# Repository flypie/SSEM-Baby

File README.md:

# SSEM-Baby

This is a work in progress.

All of the IP belongs to the Computer Conservation Society this project is purely to convert the diagrams to KiCAD as a format with greater utility. https://computerconservationsociety.org/ssemvolunteers/volunteers/index.html

I do not claim any rights whatsoever.

If anyone want to do help out with checks or corrections let me know and I'll try and work out how Merge works.

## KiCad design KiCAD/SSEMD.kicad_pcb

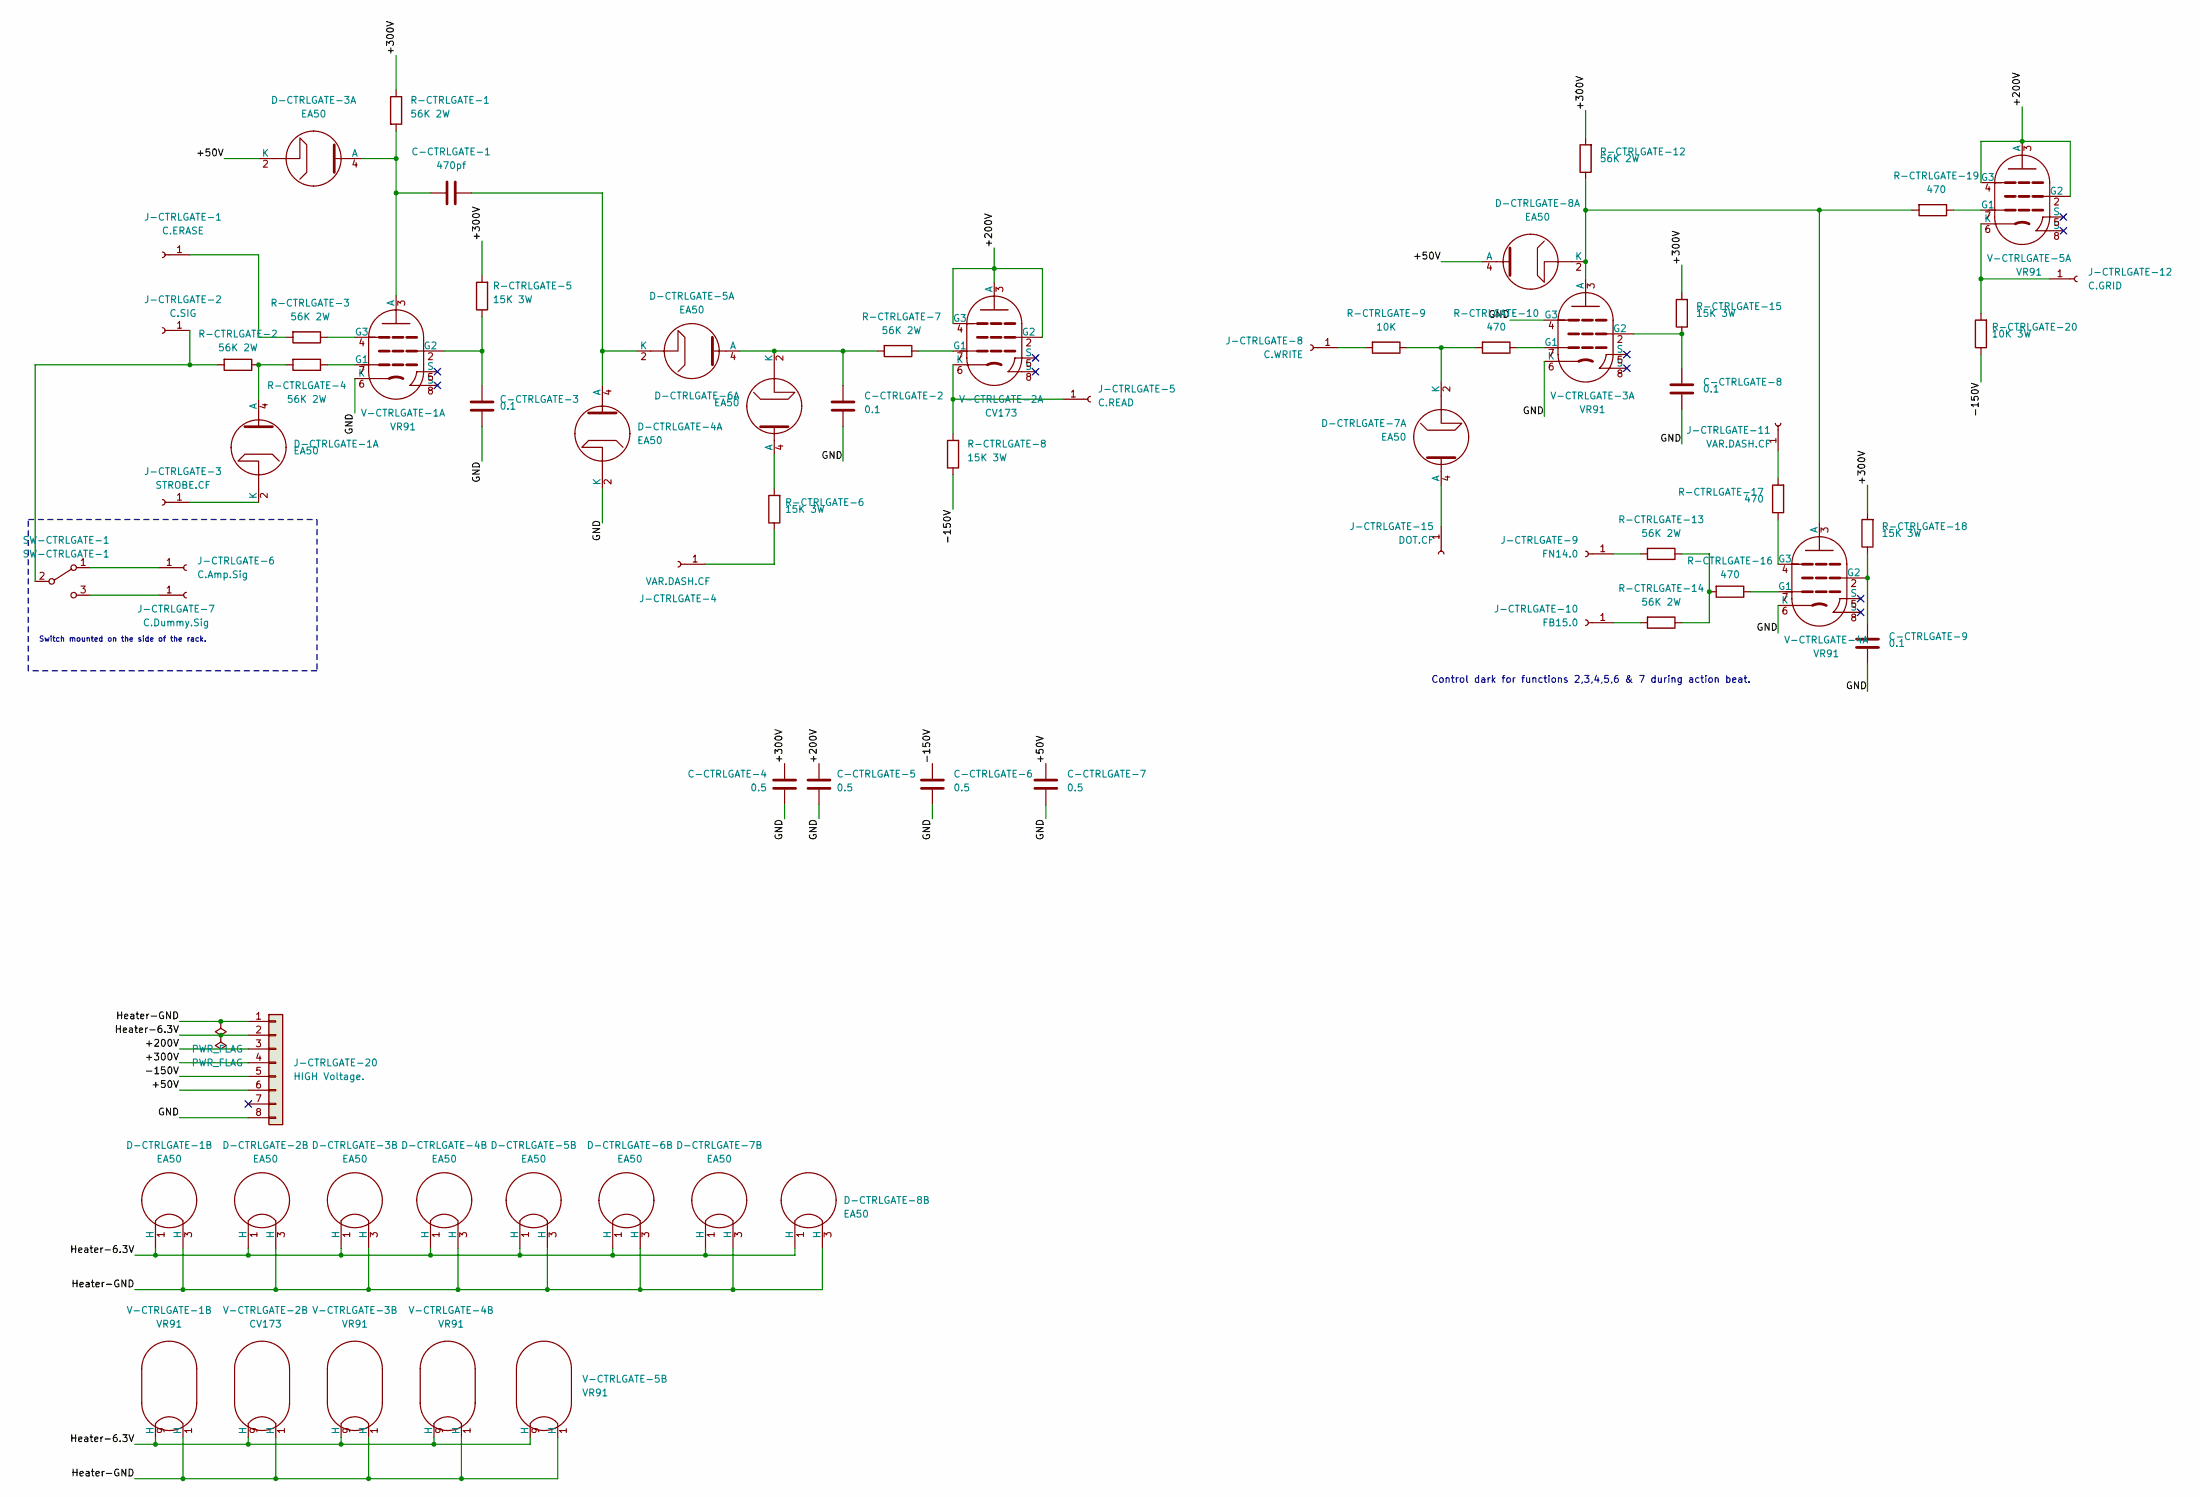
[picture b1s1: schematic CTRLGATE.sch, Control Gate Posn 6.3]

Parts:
C-CTRLGATE-1: 470pf; C_Disc_D7.5mm_W5.0mm_P5.00mm
C-CTRLGATE-2, C-CTRLGATE-3, C-CTRLGATE-8, C-CTRLGATE-9: 0.1; C_Disc_D7.5mm_W5.0mm_P5.00mm
C-CTRLGATE-4, C-CTRLGATE-5, C-CTRLGATE-6, C-CTRLGATE-7: 0.5; C_Disc_D7.5mm_W5.0mm_P5.00mm
D-CTRLGATE-1, D-CTRLGATE-2, D-CTRLGATE-3, D-CTRLGATE-4, D-CTRLGATE-5, D-CTRLGATE-6, D-CTRLGATE-7, D-CTRLGATE-8: EA50; Valve_B3G
J-CTRLGATE-1: C.ERASE; 242431
J-CTRLGATE-2: C.SIG; 242431
J-CTRLGATE-3: STROBE.CF; 242431
J-CTRLGATE-4, J-CTRLGATE-11: VAR.DASH.CF; 242431
J-CTRLGATE-5: C.READ; 242431
J-CTRLGATE-6: C.Amp.Sig; 242431
J-CTRLGATE-7: C.Dummy.Sig; 242431
J-CTRLGATE-8: C.WRITE; 242431
J-CTRLGATE-9: FN14.0; 242431
J-CTRLGATE-10: FB15.0; 242431
J-CTRLGATE-12: C.GRID; 242431
J-CTRLGATE-15: DOT.CF; 242431
J-CTRLGATE-20: HIGH Voltage.; TE_MATE-N-LOK_1-770970-x_2x04_P4.14mm_Horizontal
R-CTRLGATE-1, R-CTRLGATE-2, R-CTRLGATE-3, R-CTRLGATE-4, R-CTRLGATE-7, R-CTRLGATE-12, R-CTRLGATE-13, R-CTRLGATE-14: 56K 2W; R_Axial_DIN0516_L15.5mm_D5.0mm_P5.08mm_Vertical
R-CTRLGATE-5, R-CTRLGATE-6, R-CTRLGATE-8, R-CTRLGATE-15, R-CTRLGATE-18: 15K 3W; R_Axial_DIN0516_L15.5mm_D5.0mm_P5.08mm_Vertical
R-CTRLGATE-9: 10K; R_Axial_DIN0516_L15.5mm_D5.0mm_P5.08mm_Vertical
R-CTRLGATE-10, R-CTRLGATE-16, R-CTRLGATE-17, R-CTRLGATE-19: 470; R_Axial_DIN0516_L15.5mm_D5.0mm_P5.08mm_Vertical
R-CTRLGATE-20: 10K 3W; R_Axial_DIN0516_L15.5mm_D5.0mm_P5.08mm_Vertical
SW-CTRLGATE-1: SW-CTRLGATE-1; M2011SS1W03
V-CTRLGATE-1, V-CTRLGATE-3, V-CTRLGATE-4, V-CTRLGATE-5: VR91; Valve_9Loctal
V-CTRLGATE-2: CV173; Valve_9Loctal

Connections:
/CTRLGATE/+50V: C-CTRLGATE-7.1, D-CTRLGATE-3.2 (K), D-CTRLGATE-8.4 (A), J-CTRLGATE-20.6
/CTRLGATE/+200V: C-CTRLGATE-5.1, J-CTRLGATE-20.3, V-CTRLGATE-2.2 (G2), V-CTRLGATE-2.3 (A), V-CTRLGATE-2.4 (G3), V-CTRLGATE-5.2 (G2), V-CTRLGATE-5.3 (A), V-CTRLGATE-5.4 (G3)
/CTRLGATE/+300V: C-CTRLGATE-4.1, J-CTRLGATE-20.4, R-CTRLGATE-1.1, R-CTRLGATE-5.2, R-CTRLGATE-12.2, R-CTRLGATE-15.2, R-CTRLGATE-18.2
/CTRLGATE/-150V: C-CTRLGATE-6.2, J-CTRLGATE-20.5, R-CTRLGATE-8.1, R-CTRLGATE-20.1
/CTRLGATE/GND: C-CTRLGATE-2.2, C-CTRLGATE-3.2, C-CTRLGATE-4.2, C-CTRLGATE-5.2, C-CTRLGATE-6.1, C-CTRLGATE-7.2, C-CTRLGATE-8.2, C-CTRLGATE-9.2, D-CTRLGATE-4.2 (K), J-CTRLGATE-20.8, V-CTRLGATE-1.6 (K), V-CTRLGATE-3.4 (G3), V-CTRLGATE-3.6 (K), V-CTRLGATE-4.6 (K)
/CTRLGATE/Heater-6.3V: D-CTRLGATE-1.1 (H), D-CTRLGATE-2.1 (H), D-CTRLGATE-3.1 (H), D-CTRLGATE-4.1 (H), D-CTRLGATE-5.1 (H), D-CTRLGATE-6.1 (H), D-CTRLGATE-7.1 (H), D-CTRLGATE-8.1 (H), J-CTRLGATE-20.2, V-CTRLGATE-1.9 (H), V-CTRLGATE-2.9 (H), V-CTRLGATE-3.9 (H), V-CTRLGATE-4.9 (H), V-CTRLGATE-5.9 (H)
/CTRLGATE/Heater-GND: D-CTRLGATE-1.3 (H), D-CTRLGATE-2.3 (H), D-CTRLGATE-3.3 (H), D-CTRLGATE-4.3 (H), D-CTRLGATE-5.3 (H), D-CTRLGATE-6.3 (H), D-CTRLGATE-7.3 (H), D-CTRLGATE-8.3 (H), J-CTRLGATE-20.1, V-CTRLGATE-1.1 (H), V-CTRLGATE-2.1 (H), V-CTRLGATE-3.1 (H), V-CTRLGATE-4.1 (H), V-CTRLGATE-5.1 (H)
unnamed: C-CTRLGATE-1.1, D-CTRLGATE-3.4 (A), R-CTRLGATE-1.2, V-CTRLGATE-1.3 (A)
unnamed: C-CTRLGATE-1.2, D-CTRLGATE-4.4 (A), D-CTRLGATE-5.2 (K)
unnamed: C-CTRLGATE-2.1, D-CTRLGATE-5.4 (A), D-CTRLGATE-6.2 (K), R-CTRLGATE-7.2
unnamed: C-CTRLGATE-3.1, R-CTRLGATE-5.1, V-CTRLGATE-1.2 (G2)
unnamed: C-CTRLGATE-8.1, R-CTRLGATE-15.1, V-CTRLGATE-3.2 (G2)
unnamed: C-CTRLGATE-9.1, R-CTRLGATE-18.1, V-CTRLGATE-4.2 (G2)
unnamed: D-CTRLGATE-1.2 (K), J-CTRLGATE-3.1
unnamed: D-CTRLGATE-1.4 (A), R-CTRLGATE-2.1, R-CTRLGATE-4.2
unnamed: D-CTRLGATE-6.4 (A), R-CTRLGATE-6.2
unnamed: D-CTRLGATE-7.2 (K), R-CTRLGATE-9.1, R-CTRLGATE-10.2
unnamed: D-CTRLGATE-7.4 (A), J-CTRLGATE-15.1
unnamed: D-CTRLGATE-8.2 (K), R-CTRLGATE-12.1, R-CTRLGATE-19.2, V-CTRLGATE-3.3 (A), V-CTRLGATE-4.3 (A)
unnamed: J-CTRLGATE-1.1, R-CTRLGATE-3.2
unnamed: J-CTRLGATE-2.1, R-CTRLGATE-2.2, SW-CTRLGATE-1.2 (B)
unnamed: J-CTRLGATE-4.1, R-CTRLGATE-6.1
unnamed: J-CTRLGATE-5.1, R-CTRLGATE-8.2, V-CTRLGATE-2.6 (K)
unnamed: J-CTRLGATE-6.1, SW-CTRLGATE-1.1 (A)
unnamed: J-CTRLGATE-7.1, SW-CTRLGATE-1.3 (C)
unnamed: J-CTRLGATE-8.1, R-CTRLGATE-9.2
unnamed: J-CTRLGATE-9.1, R-CTRLGATE-13.2
unnamed: J-CTRLGATE-10.1, R-CTRLGATE-14.2
unnamed: J-CTRLGATE-11.1, R-CTRLGATE-17.2
unnamed: J-CTRLGATE-12.1, R-CTRLGATE-20.2, V-CTRLGATE-5.6 (K)
unnamed: R-CTRLGATE-3.1, V-CTRLGATE-1.4 (G3)
unnamed: R-CTRLGATE-4.1, V-CTRLGATE-1.7 (G1)
unnamed: R-CTRLGATE-7.1, V-CTRLGATE-2.7 (G1)
unnamed: R-CTRLGATE-10.1, V-CTRLGATE-3.7 (G1)
unnamed: R-CTRLGATE-13.1, R-CTRLGATE-14.1, R-CTRLGATE-16.2
unnamed: R-CTRLGATE-16.1, V-CTRLGATE-4.7 (G1)
unnamed: R-CTRLGATE-17.1, V-CTRLGATE-4.4 (G3)
unnamed: R-CTRLGATE-19.1, V-CTRLGATE-5.7 (G1)

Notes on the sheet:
Switch mounted on the side of the rack.
Control dark for functions 2,3,4,5,6 & 7 during action beat.

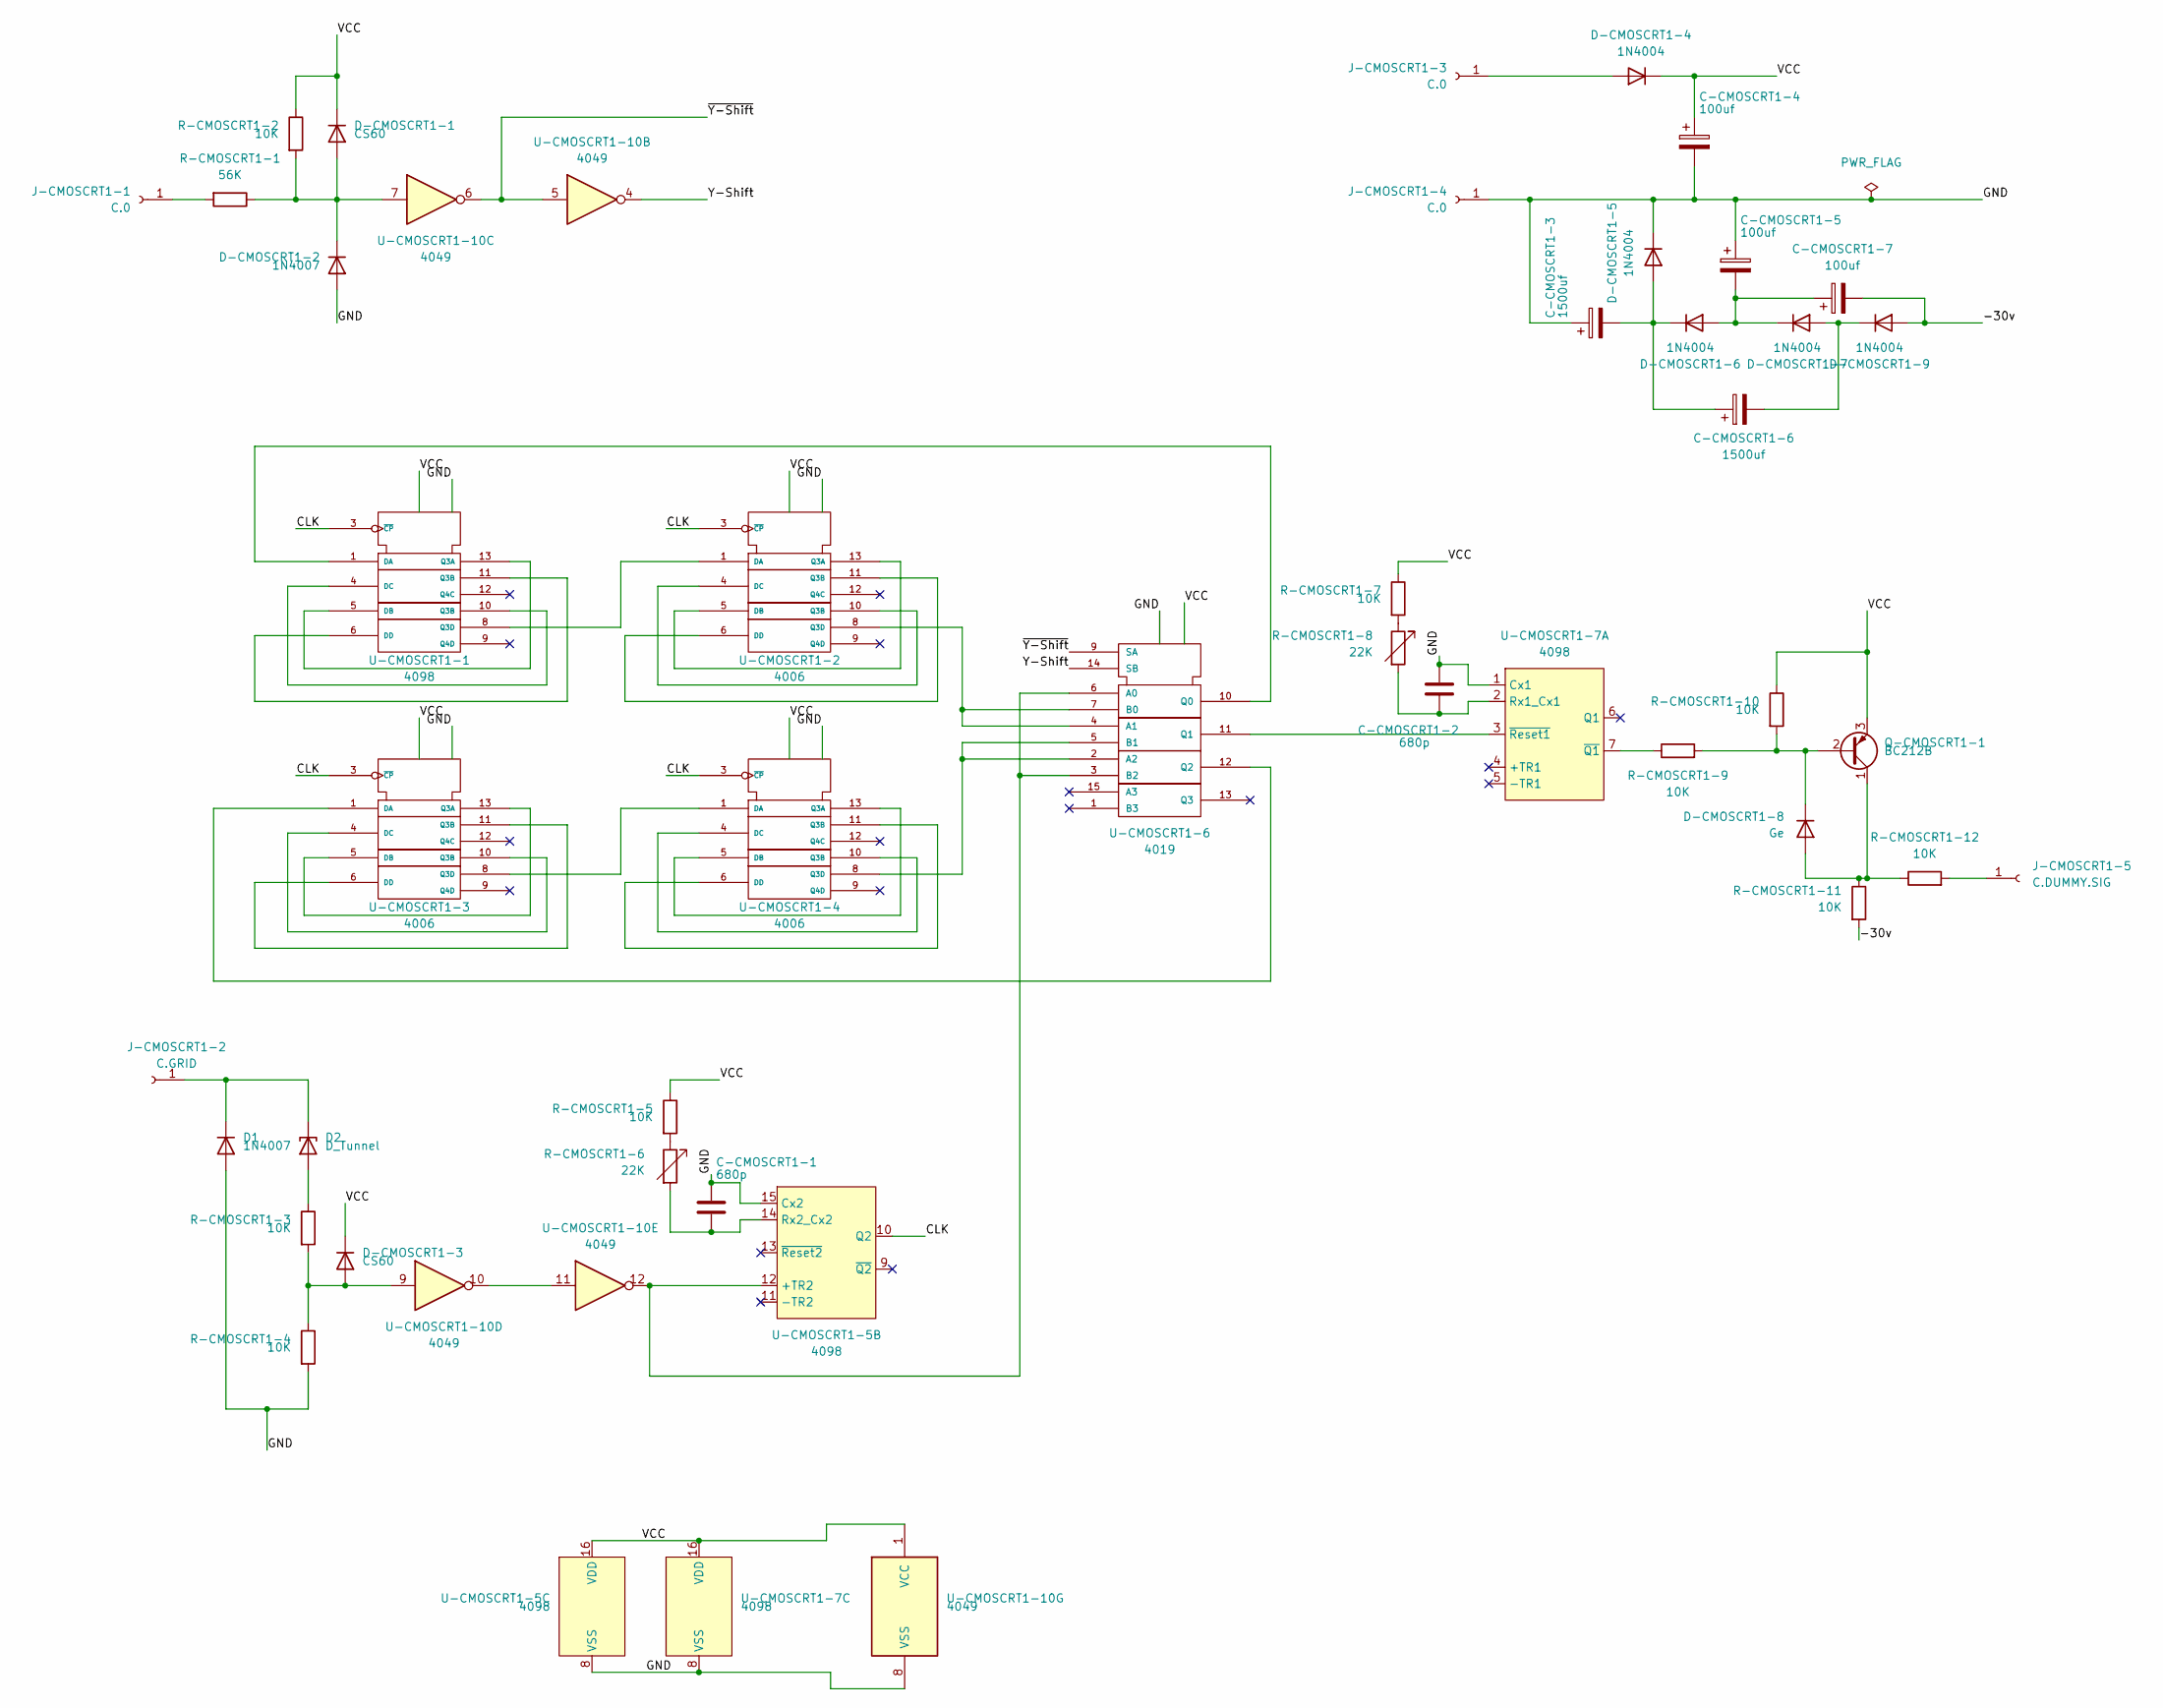
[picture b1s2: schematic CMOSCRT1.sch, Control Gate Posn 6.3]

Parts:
C-CMOSCRT1-1, C-CMOSCRT1-2: 680p; C_Disc_D7.5mm_W5.0mm_P5.00mm
C-CMOSCRT1-3, C-CMOSCRT1-6: 1500uf; C_Disc_D7.5mm_W5.0mm_P5.00mm
C-CMOSCRT1-4, C-CMOSCRT1-5, C-CMOSCRT1-7: 100uf; C_Disc_D7.5mm_W5.0mm_P5.00mm
D1: 1N4007; D_DO-41_SOD81_P10.16mm_Horizontal
D2: D_Tunnel; D_DO-201_P15.24mm_Horizontal
D-CMOSCRT1-1, D-CMOSCRT1-3: CS60; D_T-1_P5.08mm_Horizontal
D-CMOSCRT1-2: 1N4007; D_DO-41_SOD81_P10.16mm_Horizontal
D-CMOSCRT1-4, D-CMOSCRT1-5, D-CMOSCRT1-6, D-CMOSCRT1-7, D-CMOSCRT1-9: 1N4004; D_DO-41_SOD81_P10.16mm_Horizontal
D-CMOSCRT1-8: Ge; D_DO-41_SOD81_P10.16mm_Horizontal
J-CMOSCRT1-1, J-CMOSCRT1-3, J-CMOSCRT1-4: C.0; 242431
J-CMOSCRT1-2: C.GRID; 242431
J-CMOSCRT1-5: C.DUMMY.SIG; 242431
Q-CMOSCRT1-1: BC212B; TO-92_Inline
R-CMOSCRT1-1: 56K; R_Axial_DIN0516_L15.5mm_D5.0mm_P5.08mm_Vertical
R-CMOSCRT1-2, R-CMOSCRT1-3, R-CMOSCRT1-4, R-CMOSCRT1-5, R-CMOSCRT1-7, R-CMOSCRT1-9, R-CMOSCRT1-10, R-CMOSCRT1-11, R-CMOSCRT1-12: 10K; R_Axial_DIN0516_L15.5mm_D5.0mm_P5.08mm_Vertical
R-CMOSCRT1-6, R-CMOSCRT1-8: 22K; R_Axial_DIN0516_L15.5mm_D5.0mm_P5.08mm_Vertical
U-CMOSCRT1-1: 4098; DIP-14_W7.62mm
U-CMOSCRT1-2, U-CMOSCRT1-3, U-CMOSCRT1-4: 4006; DIP-14_W7.62mm
U-CMOSCRT1-5, U-CMOSCRT1-7: 4098; DIP-16_W7.62mm
U-CMOSCRT1-6: 4019; DIP-16_W7.62mm
U-CMOSCRT1-10: 4049; DIP-14_W7.62mm

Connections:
/CMOSCRT1/-30v: C-CMOSCRT1-7.2, D-CMOSCRT1-9.2 (A), R-CMOSCRT1-11.2
/CMOSCRT1/CLK: U-CMOSCRT1-1.3 (~CP), U-CMOSCRT1-2.3 (~CP), U-CMOSCRT1-3.3 (~CP), U-CMOSCRT1-4.3 (~CP), U-CMOSCRT1-5.10 (Q2)
/CMOSCRT1/Y-Shift: U-CMOSCRT1-6.14 (SB), U-CMOSCRT1-10.4
/CMOSCRT1/~Y-Shift: U-CMOSCRT1-6.9 (SA), U-CMOSCRT1-10.5, U-CMOSCRT1-10.6
unnamed: C-CMOSCRT1-1.2, R-CMOSCRT1-6.2, U-CMOSCRT1-5.14 (Rx2_Cx2)
unnamed: C-CMOSCRT1-2.2, R-CMOSCRT1-8.2, U-CMOSCRT1-7.2 (Rx1_Cx1)
unnamed: C-CMOSCRT1-3.2, C-CMOSCRT1-6.1, D-CMOSCRT1-5.2 (A), D-CMOSCRT1-6.1 (K)
unnamed: C-CMOSCRT1-5.2, C-CMOSCRT1-7.1, D-CMOSCRT1-6.2 (A), D-CMOSCRT1-7.1 (K)
unnamed: C-CMOSCRT1-6.2, D-CMOSCRT1-7.2 (A), D-CMOSCRT1-9.1 (K)
unnamed: D1.1 (K), D2.1 (K), J-CMOSCRT1-2.1
unnamed: D2.2 (A), R-CMOSCRT1-3.1
unnamed: D-CMOSCRT1-1.2 (A), D-CMOSCRT1-2.1 (K), R-CMOSCRT1-1.1, R-CMOSCRT1-2.2, U-CMOSCRT1-10.7
unnamed: D-CMOSCRT1-3.2 (A), R-CMOSCRT1-3.2, R-CMOSCRT1-4.1, U-CMOSCRT1-10.9
unnamed: D-CMOSCRT1-4.2 (A), J-CMOSCRT1-3.1
unnamed: D-CMOSCRT1-8.1 (K), Q-CMOSCRT1-1.2 (B), R-CMOSCRT1-9.2, R-CMOSCRT1-10.2
unnamed: D-CMOSCRT1-8.2 (A), Q-CMOSCRT1-1.1 (C), R-CMOSCRT1-11.1, R-CMOSCRT1-12.1
unnamed: J-CMOSCRT1-1.1, R-CMOSCRT1-1.2
unnamed: J-CMOSCRT1-5.1, R-CMOSCRT1-12.2
unnamed: R-CMOSCRT1-5.2, R-CMOSCRT1-6.1
unnamed: R-CMOSCRT1-7.2, R-CMOSCRT1-8.1
unnamed: R-CMOSCRT1-9.1, U-CMOSCRT1-7.7 (~Q1)
unnamed: U-CMOSCRT1-1.1 (DA), U-CMOSCRT1-6.10 (Q0)
unnamed: U-CMOSCRT1-1.8 (Q3D), U-CMOSCRT1-2.1 (DA)
unnamed: U-CMOSCRT1-1.4 (DC), U-CMOSCRT1-1.10 (Q3B)
unnamed: U-CMOSCRT1-1.6 (DD), U-CMOSCRT1-1.11 (Q3B)
unnamed: U-CMOSCRT1-1.5 (DB), U-CMOSCRT1-1.13 (Q3A)
unnamed: U-CMOSCRT1-2.8 (Q3D), U-CMOSCRT1-6.4 (A1), U-CMOSCRT1-6.7 (B0)
unnamed: U-CMOSCRT1-2.4 (DC), U-CMOSCRT1-2.10 (Q3B)
unnamed: U-CMOSCRT1-2.6 (DD), U-CMOSCRT1-2.11 (Q3B)
unnamed: U-CMOSCRT1-2.5 (DB), U-CMOSCRT1-2.13 (Q3A)
unnamed: U-CMOSCRT1-3.1 (DA), U-CMOSCRT1-6.12 (Q2)
unnamed: U-CMOSCRT1-3.8 (Q3D), U-CMOSCRT1-4.1 (DA)
unnamed: U-CMOSCRT1-3.4 (DC), U-CMOSCRT1-3.10 (Q3B)
unnamed: U-CMOSCRT1-3.6 (DD), U-CMOSCRT1-3.11 (Q3B)
unnamed: U-CMOSCRT1-3.5 (DB), U-CMOSCRT1-3.13 (Q3A)
unnamed: U-CMOSCRT1-4.8 (Q3D), U-CMOSCRT1-6.2 (A2), U-CMOSCRT1-6.5 (B1)
unnamed: U-CMOSCRT1-4.4 (DC), U-CMOSCRT1-4.10 (Q3B)
unnamed: U-CMOSCRT1-4.6 (DD), U-CMOSCRT1-4.11 (Q3B)
unnamed: U-CMOSCRT1-4.5 (DB), U-CMOSCRT1-4.13 (Q3A)
unnamed: U-CMOSCRT1-6.11 (Q1), U-CMOSCRT1-7.3 (~Reset1)
unnamed: U-CMOSCRT1-10.10, U-CMOSCRT1-10.11
unnamed: U-CMOSCRT1-5.12 (+TR2), U-CMOSCRT1-6.3 (B2), U-CMOSCRT1-6.6 (A0), U-CMOSCRT1-10.12
Vdd: C-CMOSCRT1-4.1, D-CMOSCRT1-1.1 (K), D-CMOSCRT1-3.1 (K), D-CMOSCRT1-4.1 (K), Q-CMOSCRT1-1.3 (E), R-CMOSCRT1-2.1, R-CMOSCRT1-5.1, R-CMOSCRT1-7.1, R-CMOSCRT1-10.1, U-CMOSCRT1-1.14 (Vdd), U-CMOSCRT1-2.14 (Vdd), U-CMOSCRT1-3.14 (Vdd), U-CMOSCRT1-4.14 (Vdd), U-CMOSCRT1-5.16 (VDD), U-CMOSCRT1-6.16 (Vdd), U-CMOSCRT1-7.16 (VDD), U-CMOSCRT1-10.1 (VCC)
Vss: C-CMOSCRT1-1.1, C-CMOSCRT1-2.1, C-CMOSCRT1-3.1, C-CMOSCRT1-4.2, C-CMOSCRT1-5.1, D1.2 (A), D-CMOSCRT1-2.2 (A), D-CMOSCRT1-5.1 (K), J-CMOSCRT1-4.1, R-CMOSCRT1-4.2, U-CMOSCRT1-1.7 (Vss), U-CMOSCRT1-2.7 (Vss), U-CMOSCRT1-3.7 (Vss), U-CMOSCRT1-4.7 (Vss), U-CMOSCRT1-5.8 (VSS), U-CMOSCRT1-5.15 (Cx2), U-CMOSCRT1-6.8 (Vss), U-CMOSCRT1-7.1 (Cx1), U-CMOSCRT1-7.8 (VSS), U-CMOSCRT1-10.8 (VSS)

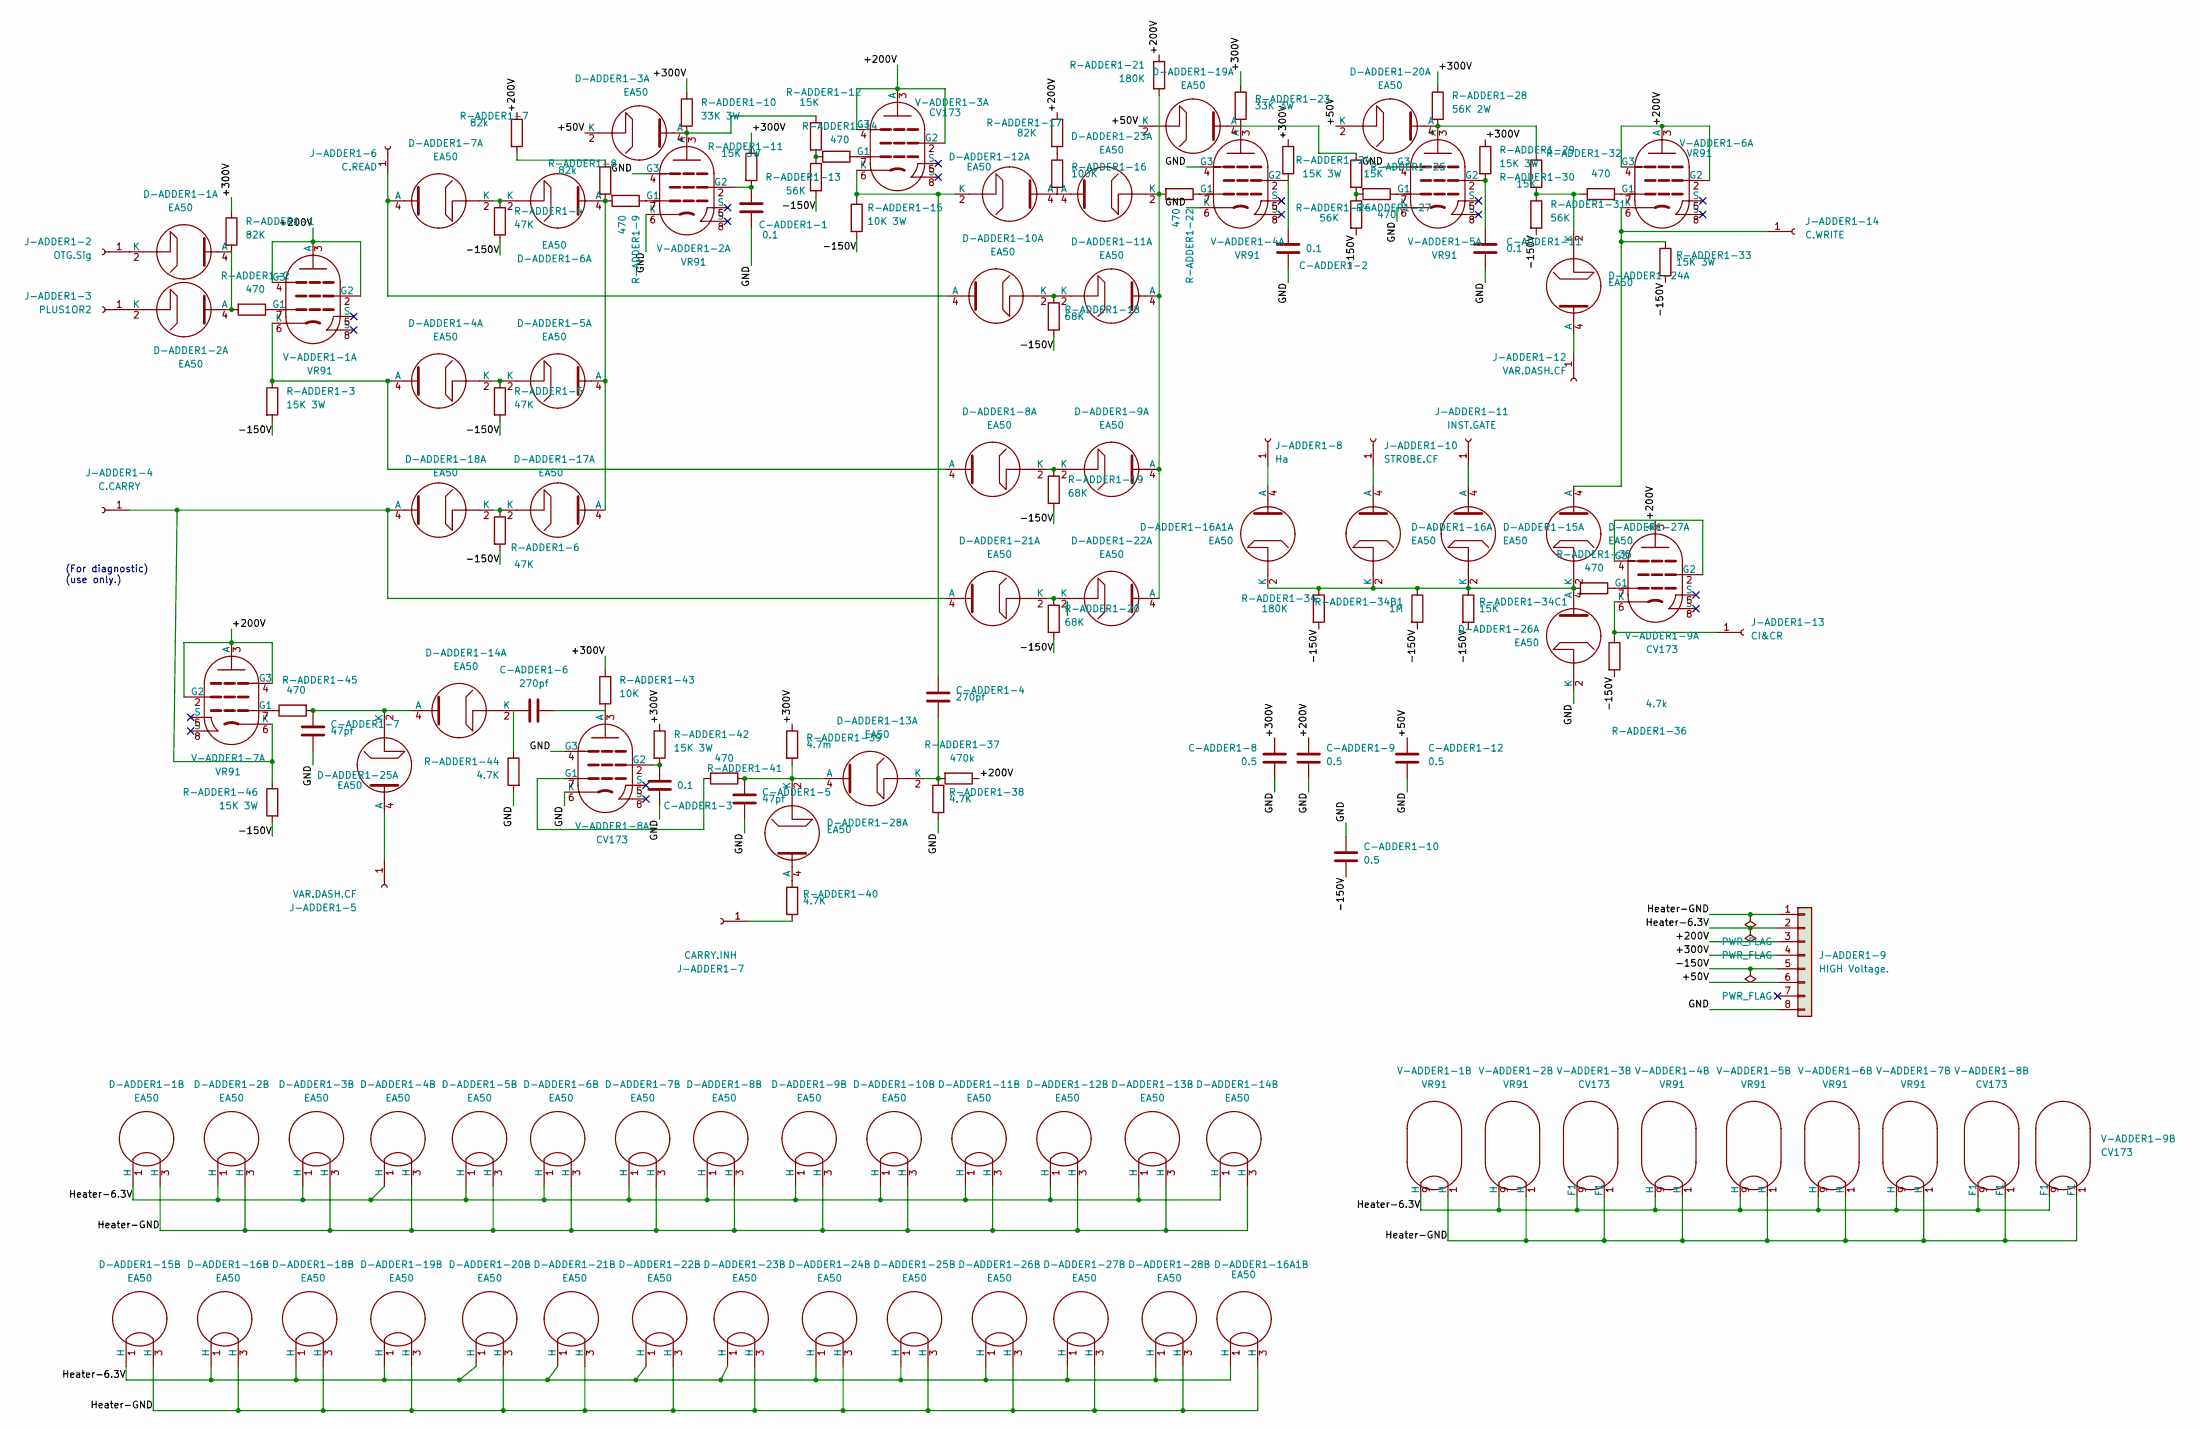
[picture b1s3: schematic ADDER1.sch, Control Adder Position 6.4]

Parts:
C-ADDER1-1, C-ADDER1-2, C-ADDER1-3, C-ADDER1-11: 0.1; C_Disc_D7.5mm_W5.0mm_P5.00mm
C-ADDER1-4, C-ADDER1-6: 270pf; C_Disc_D7.5mm_W5.0mm_P5.00mm
C-ADDER1-5, C-ADDER1-7: 47pf; C_Disc_D7.5mm_W5.0mm_P5.00mm
C-ADDER1-8, C-ADDER1-9, C-ADDER1-10, C-ADDER1-12: 0.5; C_Disc_D7.5mm_W5.0mm_P5.00mm
D-ADDER1-1, D-ADDER1-2, D-ADDER1-3, D-ADDER1-4, D-ADDER1-5, D-ADDER1-6, D-ADDER1-7, D-ADDER1-8, D-ADDER1-9, D-ADDER1-10, D-ADDER1-11, D-ADDER1-12, D-ADDER1-13, D-ADDER1-14, D-ADDER1-15, D-ADDER1-16, D-ADDER1-16A1, D-ADDER1-17, D-ADDER1-18, D-ADDER1-19, D-ADDER1-20, D-ADDER1-21, D-ADDER1-22, D-ADDER1-23, D-ADDER1-24, D-ADDER1-25, D-ADDER1-26, D-ADDER1-27, D-ADDER1-28: EA50; Valve_B3G
J-ADDER1-2: OTG.Sig; 242431
J-ADDER1-3: PLUS1OR2; 242431
J-ADDER1-4: C.CARRY; 242431
J-ADDER1-5, J-ADDER1-12: VAR.DASH.CF; 242431
J-ADDER1-6: C.READ; 242431
J-ADDER1-7: CARRY.INH; 242431
J-ADDER1-8: Ha; 242431
J-ADDER1-9: HIGH Voltage.; TE_MATE-N-LOK_1-770970-x_2x04_P4.14mm_Horizontal
J-ADDER1-10: STROBE.CF; 242431
J-ADDER1-11: INST.GATE; 242431
J-ADDER1-13: CI&CR; 242431
J-ADDER1-14: C.WRITE; 242431
R-ADDER1-1, R-ADDER1-17: 82K; R_Axial_DIN0516_L15.5mm_D5.0mm_P5.08mm_Vertical
R-ADDER1-2, R-ADDER1-9, R-ADDER1-14, R-ADDER1-22, R-ADDER1-27, R-ADDER1-32, R-ADDER1-35, R-ADDER1-41, R-ADDER1-45: 470; R_Axial_DIN0516_L15.5mm_D5.0mm_P5.08mm_Vertical
R-ADDER1-3, R-ADDER1-11, R-ADDER1-24, R-ADDER1-29, R-ADDER1-33, R-ADDER1-42, R-ADDER1-46: 15K 3W; R_Axial_DIN0516_L15.5mm_D5.0mm_P5.08mm_Vertical
R-ADDER1-4, R-ADDER1-5, R-ADDER1-6: 47K; R_Axial_DIN0516_L15.5mm_D5.0mm_P5.08mm_Vertical
R-ADDER1-7, R-ADDER1-8: 82k; R_Axial_DIN0516_L15.5mm_D5.0mm_P5.08mm_Vertical
R-ADDER1-10, R-ADDER1-23: 33K 3W; R_Axial_DIN0516_L15.5mm_D5.0mm_P5.08mm_Vertical
R-ADDER1-12, R-ADDER1-25, R-ADDER1-30, R-ADDER1-34C1: 15K; R_Axial_DIN0516_L15.5mm_D5.0mm_P5.08mm_Vertical
R-ADDER1-13, R-ADDER1-26, R-ADDER1-31: 56K; R_Axial_DIN0516_L15.5mm_D5.0mm_P5.08mm_Vertical
R-ADDER1-15: 10K 3W; R_Axial_DIN0516_L15.5mm_D5.0mm_P5.08mm_Vertical
R-ADDER1-16: 100K; R_Axial_DIN0516_L15.5mm_D5.0mm_P5.08mm_Vertical
R-ADDER1-18, R-ADDER1-19, R-ADDER1-20: 68K; R_Axial_DIN0516_L15.5mm_D5.0mm_P5.08mm_Vertical
R-ADDER1-21, R-ADDER1-34: 180K; R_Axial_DIN0516_L15.5mm_D5.0mm_P5.08mm_Vertical
R-ADDER1-28: 56K 2W; R_Axial_DIN0516_L15.5mm_D5.0mm_P5.08mm_Vertical
R-ADDER1-34B1: 1M; R_Axial_DIN0516_L15.5mm_D5.0mm_P5.08mm_Vertical
R-ADDER1-36: 4.7k; R_Axial_DIN0516_L15.5mm_D5.0mm_P5.08mm_Vertical
R-ADDER1-37: 470k; R_Axial_DIN0516_L15.5mm_D5.0mm_P5.08mm_Vertical
R-ADDER1-38, R-ADDER1-40, R-ADDER1-44: 4.7K; R_Axial_DIN0516_L15.5mm_D5.0mm_P5.08mm_Vertical
R-ADDER1-39: 4.7m; R_Axial_DIN0516_L15.5mm_D5.0mm_P5.08mm_Vertical
R-ADDER1-43: 10K; R_Axial_DIN0516_L15.5mm_D5.0mm_P5.08mm_Vertical
V-ADDER1-1, V-ADDER1-2, V-ADDER1-4, V-ADDER1-5, V-ADDER1-6, V-ADDER1-7: VR91; Valve_9Loctal
V-ADDER1-3, V-ADDER1-8, V-ADDER1-9: CV173; Valve_9Loctal

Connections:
/ADDER1/+50V: C-ADDER1-12.1, D-ADDER1-3.2 (K), D-ADDER1-19.2 (K), D-ADDER1-20.2 (K), J-ADDER1-9.6
/ADDER1/+200V: C-ADDER1-9.1, J-ADDER1-9.3, R-ADDER1-7.1, R-ADDER1-17.1, R-ADDER1-21.1, R-ADDER1-37.1, V-ADDER1-1.2 (G2), V-ADDER1-1.3 (A), V-ADDER1-1.4 (G3), V-ADDER1-3.2 (G2), V-ADDER1-3.3 (A), V-ADDER1-3.4 (G3), V-ADDER1-6.2 (G2), V-ADDER1-6.3 (A), V-ADDER1-6.4 (G3), V-ADDER1-7.2 (G2), V-ADDER1-7.3 (A), V-ADDER1-7.4 (G3), V-ADDER1-9.2 (G2), V-ADDER1-9.3 (A), V-ADDER1-9.4 (G3)
/ADDER1/+300V: C-ADDER1-8.1, J-ADDER1-9.4, R-ADDER1-1.1, R-ADDER1-10.1, R-ADDER1-11.1, R-ADDER1-23.1, R-ADDER1-24.1, R-ADDER1-28.1, R-ADDER1-29.1, R-ADDER1-39.1, R-ADDER1-42.1, R-ADDER1-43.1
/ADDER1/-150V: C-ADDER1-10.2, J-ADDER1-9.5, R-ADDER1-3.2, R-ADDER1-4.2, R-ADDER1-5.2, R-ADDER1-6.2, R-ADDER1-13.2, R-ADDER1-15.2, R-ADDER1-18.2, R-ADDER1-19.2, R-ADDER1-20.2, R-ADDER1-26.2, R-ADDER1-31.2, R-ADDER1-33.2, R-ADDER1-34.2, R-ADDER1-34B1.2, R-ADDER1-34C1.2, R-ADDER1-36.2, R-ADDER1-46.2
/ADDER1/GND: C-ADDER1-1.2, C-ADDER1-2.2, C-ADDER1-3.2, C-ADDER1-5.2, C-ADDER1-7.2, C-ADDER1-8.2, C-ADDER1-9.2, C-ADDER1-10.1, C-ADDER1-11.2, C-ADDER1-12.2, D-ADDER1-26.2 (K), J-ADDER1-9.8, R-ADDER1-38.1, R-ADDER1-44.2, V-ADDER1-2.4 (G3), V-ADDER1-2.6 (K), V-ADDER1-4.4 (G3), V-ADDER1-4.6 (K), V-ADDER1-5.4 (G3), V-ADDER1-5.6 (K), V-ADDER1-8.4 (G3), V-ADDER1-8.6 (K)
/ADDER1/Heater-6.3V: D-ADDER1-1.1 (H), D-ADDER1-2.1 (H), D-ADDER1-3.1 (H), D-ADDER1-4.1 (H), D-ADDER1-5.1 (H), D-ADDER1-6.1 (H), D-ADDER1-7.1 (H), D-ADDER1-8.1 (H), D-ADDER1-9.1 (H), D-ADDER1-10.1 (H), D-ADDER1-11.1 (H), D-ADDER1-12.1 (H), D-ADDER1-13.1 (H), D-ADDER1-14.1 (H), D-ADDER1-15.1 (H), D-ADDER1-16.1 (H), D-ADDER1-16A1.1 (H), D-ADDER1-18.1 (H), D-ADDER1-19.1 (H), D-ADDER1-20.1 (H), D-ADDER1-21.1 (H), D-ADDER1-22.1 (H), D-ADDER1-23.1 (H), D-ADDER1-24.1 (H), D-ADDER1-25.1 (H), D-ADDER1-26.1 (H), D-ADDER1-27.1 (H), D-ADDER1-28.1 (H), J-ADDER1-9.2, V-ADDER1-1.9 (H), V-ADDER1-2.9 (H), V-ADDER1-3.9 (F1), V-ADDER1-4.9 (H), V-ADDER1-5.9 (H), V-ADDER1-6.9 (H), V-ADDER1-7.9 (H), V-ADDER1-8.9 (F1), V-ADDER1-9.9 (F1)
/ADDER1/Heater-GND: D-ADDER1-1.3 (H), D-ADDER1-2.3 (H), D-ADDER1-3.3 (H), D-ADDER1-4.3 (H), D-ADDER1-5.3 (H), D-ADDER1-6.3 (H), D-ADDER1-7.3 (H), D-ADDER1-8.3 (H), D-ADDER1-9.3 (H), D-ADDER1-10.3 (H), D-ADDER1-11.3 (H), D-ADDER1-12.3 (H), D-ADDER1-13.3 (H), D-ADDER1-14.3 (H), D-ADDER1-15.3 (H), D-ADDER1-16.3 (H), D-ADDER1-16A1.3 (H), D-ADDER1-18.3 (H), D-ADDER1-19.3 (H), D-ADDER1-20.3 (H), D-ADDER1-21.3 (H), D-ADDER1-22.3 (H), D-ADDER1-23.3 (H), D-ADDER1-24.3 (H), D-ADDER1-25.3 (H), D-ADDER1-26.3 (H), D-ADDER1-27.3 (H), D-ADDER1-28.3 (H), J-ADDER1-9.1, V-ADDER1-1.1 (H), V-ADDER1-2.1 (H), V-ADDER1-3.1 (F1), V-ADDER1-4.1 (H), V-ADDER1-5.1 (H), V-ADDER1-6.1 (H), V-ADDER1-7.1 (H), V-ADDER1-8.1 (F1), V-ADDER1-9.1 (F1)
unnamed: C-ADDER1-1.1, R-ADDER1-11.2, V-ADDER1-2.2 (G2)
unnamed: C-ADDER1-2.1, R-ADDER1-24.2, V-ADDER1-4.2 (G2)
unnamed: C-ADDER1-3.1, R-ADDER1-42.2, V-ADDER1-8.2 (G2)
unnamed: C-ADDER1-4.1, D-ADDER1-12.2 (K), R-ADDER1-15.1, V-ADDER1-3.6 (K)
unnamed: C-ADDER1-4.2, D-ADDER1-13.2 (K), R-ADDER1-37.2, R-ADDER1-38.2
unnamed: C-ADDER1-5.1, D-ADDER1-13.4 (A), D-ADDER1-28.2 (K), R-ADDER1-39.2, R-ADDER1-41.1
unnamed: C-ADDER1-6.1, R-ADDER1-43.2, V-ADDER1-8.3 (A)
unnamed: C-ADDER1-6.2, D-ADDER1-14.2 (K), R-ADDER1-44.1
unnamed: C-ADDER1-7.1, D-ADDER1-14.4 (A), D-ADDER1-25.2 (K), R-ADDER1-45.2
unnamed: C-ADDER1-11.1, R-ADDER1-29.2, V-ADDER1-5.2 (G2)
unnamed: D-ADDER1-1.2 (K), J-ADDER1-2.1
unnamed: D-ADDER1-1.4 (A), D-ADDER1-2.4 (A), R-ADDER1-1.2, R-ADDER1-2.2
unnamed: D-ADDER1-2.2 (K), J-ADDER1-3.1
unnamed: D-ADDER1-3.4 (A), R-ADDER1-10.2, R-ADDER1-12.1, V-ADDER1-2.3 (A)
unnamed: D-ADDER1-4.2 (K), D-ADDER1-5.2 (K), R-ADDER1-5.1
unnamed: D-ADDER1-4.4 (A), D-ADDER1-8.4 (A), R-ADDER1-3.1, V-ADDER1-1.6 (K)
unnamed: D-ADDER1-6.2 (K), D-ADDER1-7.2 (K), R-ADDER1-4.1
unnamed: D-ADDER1-8.2 (K), D-ADDER1-9.2 (K), R-ADDER1-19.1
unnamed: D-ADDER1-10.2 (K), D-ADDER1-11.2 (K), R-ADDER1-18.1
unnamed: D-ADDER1-7.4 (A), D-ADDER1-10.4 (A), J-ADDER1-6.1
unnamed: D-ADDER1-9.4 (A), D-ADDER1-11.4 (A), D-ADDER1-22.4 (A), D-ADDER1-23.2 (K), R-ADDER1-21.2, R-ADDER1-22.2
unnamed: D-ADDER1-12.4 (A), D-ADDER1-23.4 (A), R-ADDER1-16.2
unnamed: D-ADDER1-15.2 (K), D-ADDER1-16.2 (K), D-ADDER1-16A1.2 (K), D-ADDER1-26.4 (A), D-ADDER1-27.2 (K), R-ADDER1-34.1, R-ADDER1-34B1.1, R-ADDER1-34C1.1, R-ADDER1-35.2
unnamed: D-ADDER1-15.4 (A), J-ADDER1-11.1
unnamed: D-ADDER1-16.4 (A), J-ADDER1-10.1
unnamed: D-ADDER1-16A1.4 (A), J-ADDER1-8.1
unnamed: D-ADDER1-17.2 (K), D-ADDER1-18.2 (K), R-ADDER1-6.1
unnamed: D-ADDER1-5.4 (A), D-ADDER1-6.4 (A), D-ADDER1-17.4 (A), R-ADDER1-8.2, R-ADDER1-9.2
unnamed: D-ADDER1-18.4 (A), D-ADDER1-21.4 (A), J-ADDER1-4.1, R-ADDER1-46.1, V-ADDER1-7.6 (K)
unnamed: D-ADDER1-19.4 (A), R-ADDER1-23.2, R-ADDER1-25.1, V-ADDER1-4.3 (A)
unnamed: D-ADDER1-20.4 (A), R-ADDER1-28.2, R-ADDER1-30.1, V-ADDER1-5.3 (A)
unnamed: D-ADDER1-21.2 (K), D-ADDER1-22.2 (K), R-ADDER1-20.1
unnamed: D-ADDER1-24.2 (K), R-ADDER1-30.2, R-ADDER1-31.1, R-ADDER1-32.2
unnamed: D-ADDER1-24.4 (A), J-ADDER1-12.1
unnamed: D-ADDER1-25.4 (A), J-ADDER1-5.1
unnamed: D-ADDER1-27.4 (A), J-ADDER1-14.1, R-ADDER1-33.1, V-ADDER1-6.6 (K)
unnamed: D-ADDER1-28.4 (A), R-ADDER1-40.2
unnamed: J-ADDER1-7.1, R-ADDER1-40.1
unnamed: J-ADDER1-13.1, R-ADDER1-36.1, V-ADDER1-9.6 (K)
unnamed: R-ADDER1-2.1, V-ADDER1-1.7 (G1)
unnamed: R-ADDER1-7.2, R-ADDER1-8.1
unnamed: R-ADDER1-9.1, V-ADDER1-2.7 (G1)
unnamed: R-ADDER1-12.2, R-ADDER1-13.1, R-ADDER1-14.2
unnamed: R-ADDER1-14.1, V-ADDER1-3.7 (G1)
unnamed: R-ADDER1-16.1, R-ADDER1-17.2
unnamed: R-ADDER1-22.1, V-ADDER1-4.7 (G1)
unnamed: R-ADDER1-25.2, R-ADDER1-26.1, R-ADDER1-27.2
unnamed: R-ADDER1-27.1, V-ADDER1-5.7 (G1)
unnamed: R-ADDER1-32.1, V-ADDER1-6.7 (G1)
unnamed: R-ADDER1-35.1, V-ADDER1-9.7 (G1)
unnamed: R-ADDER1-41.2, V-ADDER1-8.7 (G1)
unnamed: R-ADDER1-45.1, V-ADDER1-7.7 (G1)

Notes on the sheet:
(For diagnostic) (use only.)
